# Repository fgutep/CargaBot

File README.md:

# CargaBot - Open Source ROS2 Forklift Platform

> **This is an active development project** - Originally started as a TurtleBot Burger clone, this project has evolved into a four-level forklift (montacargas) robot designed for object classification and manipulation.

An open-source, differential drive forklift robot designed to identify, pick up, and classify colored cubes (green, red, blue) using computer vision. By transitioning from a standard mobile base to a forklift architecture, CargaBot provides superior mechanical stability and simplified vertical positioning compared to traditional multi-degree-of-freedom robotic arms.

## Project Goals

- **Accessible**: Built using affordable components like the Raspberry Pi 5, ESP32 microcontrollers, and fully 3D-printable parts.
- **Educational**: A hands-on platform for learning ROS2, computer vision (YOLOv8), embedded systems, and robot kinematics.
- **Object Manipulation**: Features a custom-built elevator mechanism specifically designed for picking up and stacking objects in a laboratory environment.
- **Distributed Processing**: Utilizes remote PC processing for heavy computer vision tasks to maintain real-time operational efficiency on the robot itself.

## Bill of Materials

### Electronics
- **Main Computer**: Raspberry Pi 5 (8GB) - Serves as the primary system processor and runs the ROS2 middleware.
- **Motion Controller**: ESP32-S3 (Dual-core, 240 MHz) - Manages the wheel odometry and traction bridge.
- **Lift & Sensor Controller**: Custom Waveshare ESP32-S3 Zero PCB - Handles $I^{2}C$ multiplexing and elevator control signals.
- **Sensors**: 5x VL53L0X Time-of-Flight sensors - Four provide lateral obstacle avoidance, while the fifth measures the elevator's height.
- **Vision**: Raspberry Pi Camera Module (5 MP, CSI interface) - Oriented downward to capture objects for the vision model.
- **Motors (Traction)**: 2x DC motors with integrated encoders for precise odometry.
- **Motor (Lift)**: 5V Stepper motor for driving the vertical elevator mechanism.
- **Drivers**: Two DRV8833 drivers (configured in parallel to handle higher current) for traction, and a dedicated 5V stepper driver for the lift.

### Mechanical
- **Chassis**: Custom 4-level 3D-printed PLA structure connected by structural support rods for dynamic rigidity.
- **Elevator System**: Driven by a T8 4-start lead screw, supported by upper and lower mechanical limit switches (end-stops) for safe positioning.
- **Wheels**: Custom PLA-printed wheels equipped with TPU treads to significantly improve traction and reduce slipping.

## Key Features & Architecture

### Hardware: The 4-Level Design
- **Level 1 (Base)**: Houses the traction motors, the TPU-treaded wheels, and four VL53L0X ToF sensors pointing forward, backward, left, and right for obstacle avoidance.
- **Level 2 (Electronic Control)**: Contains the main ESP32-S3 board, the parallel DRV8833 motor drivers, and decoupling capacitors.
- **Level 3 (Computation)**: Holds the Raspberry Pi 5 and a vertically positioned fifth VL53L0X sensor used to continuously track the elevator's height without signal interference.
- **Level 4 (Elevator System)**: Accommodates the Pi Camera, the 5V stepper motor driver, and the custom Waveshare ESP32-S3 Zero PCB used for the $I^{2}C$ multiplexing.

### Software
- **ROS2 Middleware**: Relies on a full ROS2 communication suite managing synchronized, distributed nodes.
- **Dual Serial Bridges**: Operates two independent communication bridges; one dedicated to wheel odometry/positioning, and a new "Zero" bridge for exposing the five ToF sensors and the lift state.
- **Distributed YOLOv8 Vision**: Local YOLOv8 inference saturated the Raspberry Pi 5 CPU (reaching 97%), making it impossible to run other nodes simultaneously. To solve this, video is streamed continuously via GStreamer (RTSP protocol) to a desktop computer. The PC runs the YOLOv8 model in real-time and publishes the detection results (class, confidence, and coordinates) back to the robot via ROS2 messages.

## Known Issues & Future Improvements

- **Lift Speed**: The current 5V stepper motor provides precision but is very slow, taking approximately 90 seconds to elevate the platform 15 cm. A planned improvement is to replace this with a more powerful DC motor coupled with gears.
- **Low-Speed PID Control**: The traction PID control has a sensitive minimum PWM threshold and behaves abruptly at low speeds. Upgrading to higher-capacity drivers and further tuning is planned for future iterations.
- **Vision Latency**: While running inference on the PC's GPU is highly efficient, the RTSP video transmission introduces around 200 ms of latency. Future optimizations will explore video compression and hardware acceleration on the Pi 5 to reduce this delay.

## Repository Structure
*(Structure is currently being reorganized to accommodate the new dual-firmware and 4-level chassis files)*

## Getting Started
### Prerequisites
- 3D printer (PLA for chassis components, TPU for wheel treads).
- ROS2 installation (Humble recommended).
- A remote PC with a dedicated GPU for YOLOv8 processing.

*Detailed wiring and build instructions for the 4-level chassis coming soon!*

## Contributing
We welcome contributions! Please open an issue or pull request if you'd like to contribute.

## License
This project is open-source and available under the [MIT License](LICENSE).

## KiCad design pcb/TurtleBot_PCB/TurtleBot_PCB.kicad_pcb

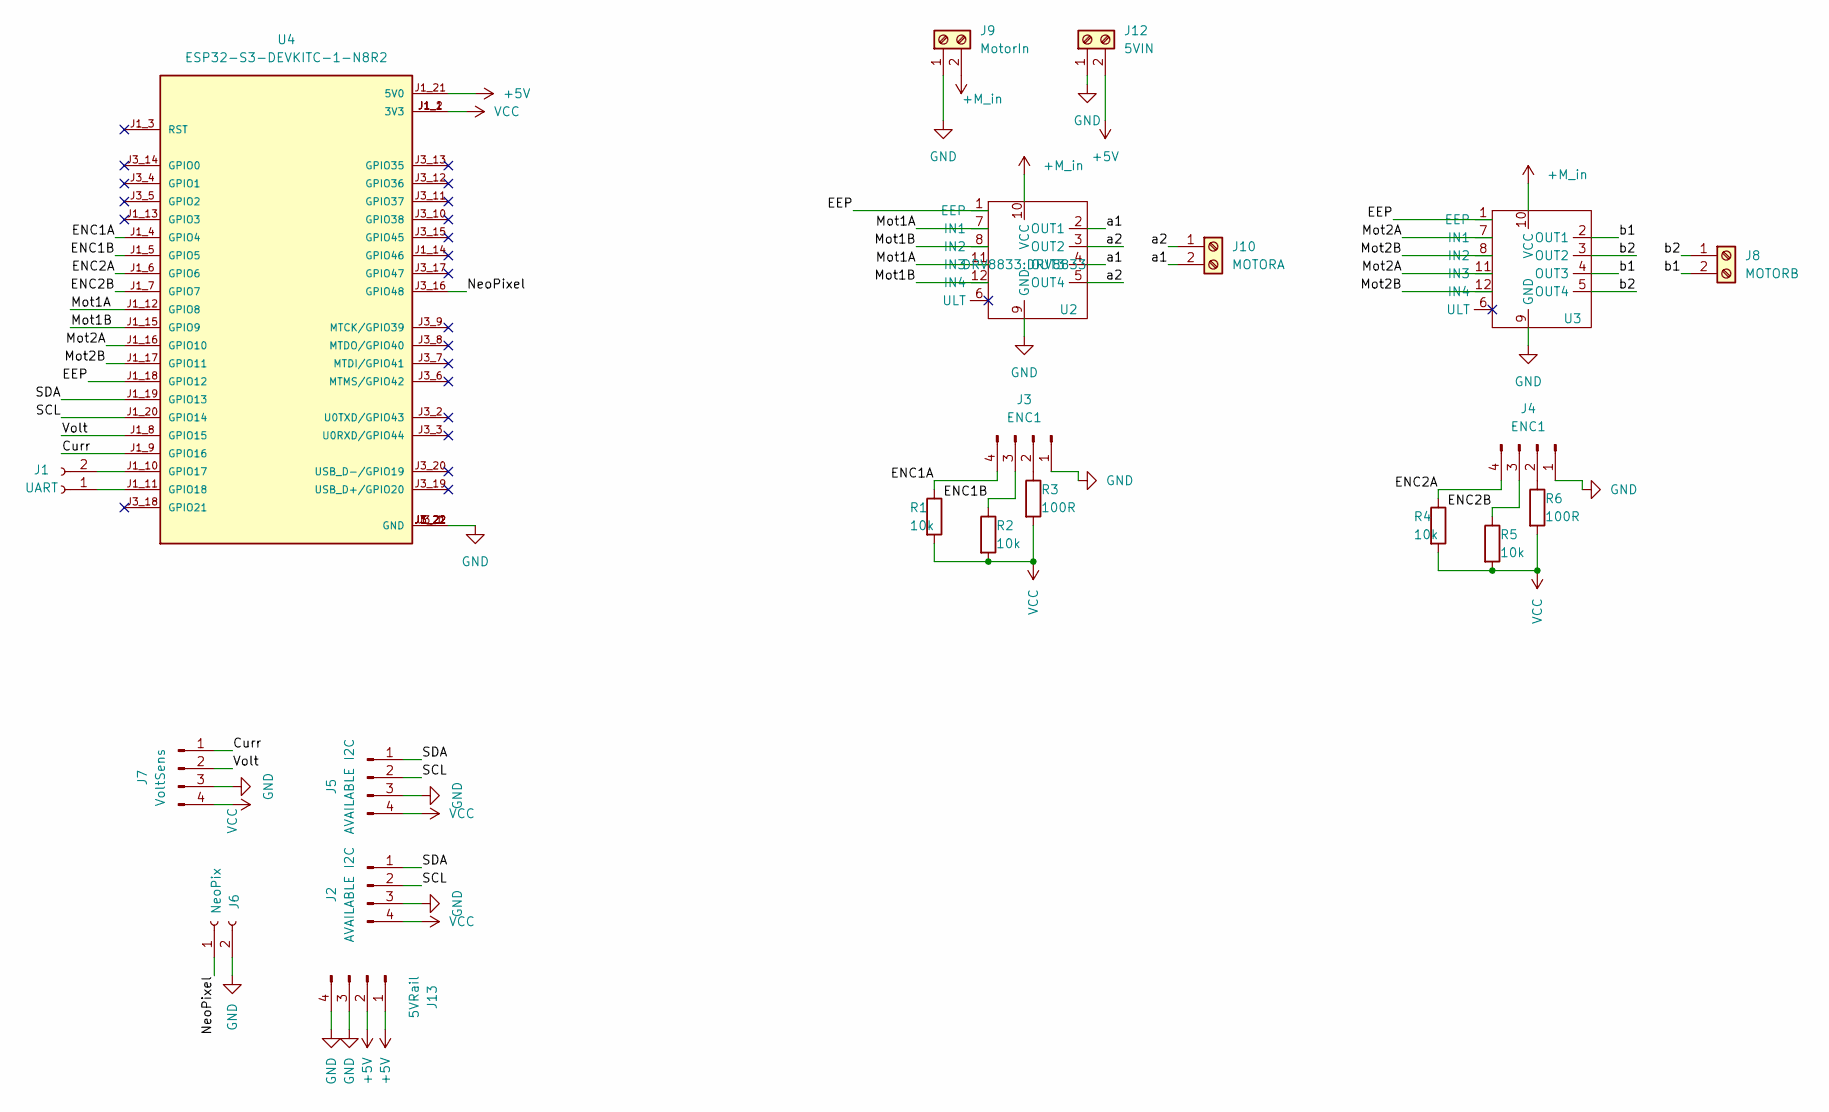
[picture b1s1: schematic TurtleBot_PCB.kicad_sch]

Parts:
J1: UART; JST_EH_B2B-EH-A_1x02_P2.50mm_Vertical
J2, J5: AVAILABLE I2C; JST_EH_B4B-EH-A_1x04_P2.50mm_Vertical
J3, J4: ENC1; JST_EH_B4B-EH-A_1x04_P2.50mm_Vertical
J6: NeoPix; JST_EH_B2B-EH-A_1x02_P2.50mm_Vertical
J7: VoltSens; JST_EH_B4B-EH-A_1x04_P2.50mm_Vertical
J8: MOTORB; TerminalBlock_4Ucon_1x02_P3.50mm_Vertical
J9: MotorIn; TerminalBlock_4Ucon_1x02_P3.50mm_Vertical
J10: MOTORA; TerminalBlock_4Ucon_1x02_P3.50mm_Vertical
J12: 5VIN; TerminalBlock_4Ucon_1x02_P3.50mm_Vertical
J13: 5VRail; PinHeader_1x04_P2.54mm_Vertical
R1, R2, R4, R5: 10k; R_Axial_DIN0207_L6.3mm_D2.5mm_P10.16mm_Horizontal
R3, R6: 100R; R_Axial_DIN0207_L6.3mm_D2.5mm_P10.16mm_Horizontal
U2, U3: DRV8833
U4: ESP32-S3-DEVKITC-1-N8R2; PARTREV V1

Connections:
+5V: J12.2, J13.1, J13.2, U4.J1_21 (5V0)
+M_in: J9.2, U2.10 (VCC), U3.10 (VCC)
/Curr: J7.1, U4.J1_9 (GPIO16)
/EEP: U2.1 (EEP), U3.1 (EEP), U4.J1_18 (GPIO12)
/ENC1A: J3.4, R1.1, U4.J1_4 (GPIO4)
/ENC1B: J3.3, R2.1, U4.J1_5 (GPIO5)
/ENC2A: J4.4, R4.1, U4.J1_6 (GPIO6)
/ENC2B: J4.3, R5.1, U4.J1_7 (GPIO7)
/Mot1A: U2.7 (IN1), U2.11 (IN3), U4.J1_12 (GPIO8)
/Mot1B: U2.8 (IN2), U2.12 (IN4), U4.J1_15 (GPIO9)
/Mot2A: U3.7 (IN1), U3.11 (IN3), U4.J1_16 (GPIO10)
/Mot2B: U3.8 (IN2), U3.12 (IN4), U4.J1_17 (GPIO11)
/NeoPixel: J6.1, U4.J3_16 (GPIO48)
/SCL: J2.2, J5.2, U4.J1_20 (GPIO14)
/SDA: J2.1, J5.1, U4.J1_19 (GPIO13)
/Volt: J7.2, U4.J1_8 (GPIO15)
/a1: J10.2, U2.2 (OUT1), U2.4 (OUT3)
/a2: J10.1, U2.3 (OUT2), U2.5 (OUT4)
/b1: J8.2, U3.2 (OUT1), U3.4 (OUT3)
/b2: J8.1, U3.3 (OUT2), U3.5 (OUT4)
GND: J2.3, J3.1, J4.1, J5.3, J6.2, J7.3, J9.1, J12.1, J13.3, J13.4, U2.9 (GND), U3.9 (GND), U4.J1_22 (GND), U4.J3_1 (GND), U4.J3_21 (GND), U4.J3_22 (GND)
unnamed: J1.1, U4.J1_11 (GPIO18)
unnamed: J1.2, U4.J1_10 (GPIO17)
unnamed: J3.2, R3.1
unnamed: J4.2, R6.1
VCC: J2.4, J5.4, J7.4, R1.2, R2.2, R3.2, R4.2, R5.2, R6.2, U4.J1_1 (3V3), U4.J1_2 (3V3)

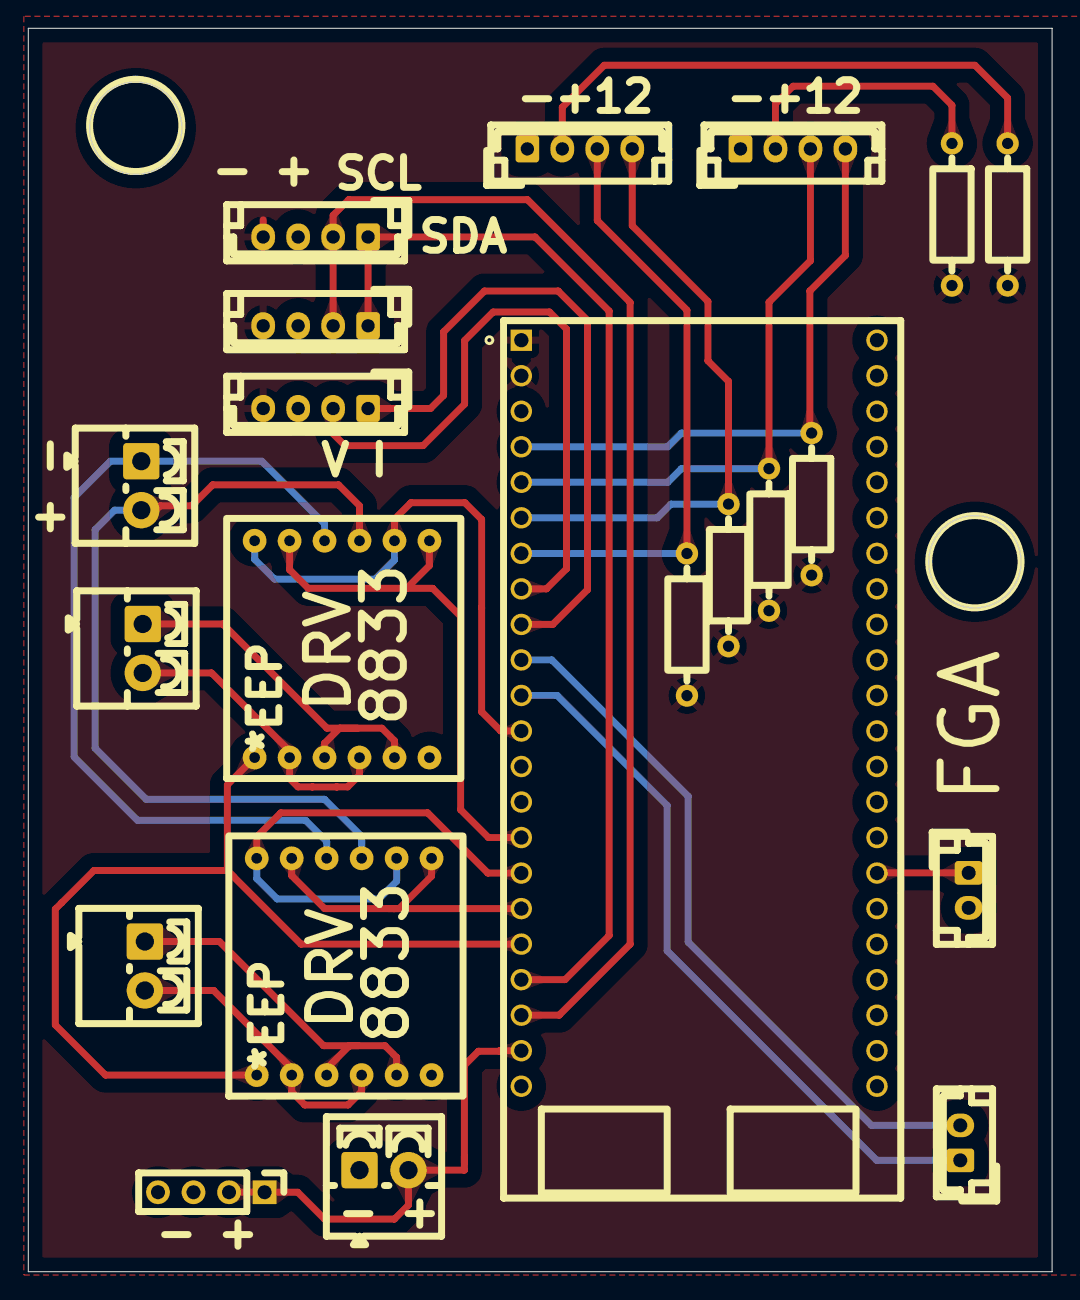
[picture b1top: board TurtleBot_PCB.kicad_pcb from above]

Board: 2 copper layers, 73.2 x 88.9 mm, 21 parts (0 on the bottom side), 26 nets.

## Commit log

2026-01-26 Revise README for TurtleBot Burger project
    Expanded README to include detailed project goals, bill of materials, key features, known issues, build steps, and contributing guidelines.
2026-01-26 Rename 3d_model.jpg.jpeg to 3d_model.jpg
2026-01-26 Archivos 3d
2026-03-11 Add AI Coder Guidelines for ESP32 Motor Control
2026-03-15 Rename firmware_v2.01 to firmware_v2.01.ino
2026-03-15 Add ROS 2 Robot Setup & Operation Guide
    Added a comprehensive guide for setting up and operating a ROS 2 robot, including workspace building, hardware configuration, running nodes, networking, and Foxglove Studio integration.
2026-04-22 Nodo ToFs
2026-04-22 Arduino Code
2026-04-24 added modelo de recon.Visual
2026-04-24 added streamable video server
2026-04-25 Cosas Raspi
2026-04-29 Add README.md file for CAD project
2026-04-29 Se agrego el cad de la ultima iteracion
2026-04-29 Create carpeta planos
2026-04-29 Revise README for CargaBot project details
    Updated project details from TurtleBot Burger to CargaBot, emphasizing its capabilities as a ROS2 forklift platform. Revised sections on project goals, hardware, software, known issues, and getting s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
2026-04-29 Main Picture Uploaded
2026-04-29 Add image of CargaBot to README
    Added an image of CargaBot to the README for better visualization.
2026-05-14 Firmware V3.0 de PCB motores y Scripts calib_lineal
2026-05-14 docs: ignore vscode in gitignore
2026-05-14 Commit Git Stash
2026-05-14 SafetyCommit
2026-05-15 Agregar lift_test_code a Arduino/lift_code
2026-05-15 v2 lift code
2026-05-16 Add latest_motion_controller.py for CargaBot
    Implement CargaBot Motion Controller with ROS2 service and parameters.
2026-05-25 Claudio se mueve solitooo :D
2026-05-25 Added WatchDog to Serial Bridge
2026-05-25 Rollback to commit 06988ff72f2baea1e2d8a15dce9c5cdb37e9bf6f
2026-05-27 Teleop now has Lift Control
